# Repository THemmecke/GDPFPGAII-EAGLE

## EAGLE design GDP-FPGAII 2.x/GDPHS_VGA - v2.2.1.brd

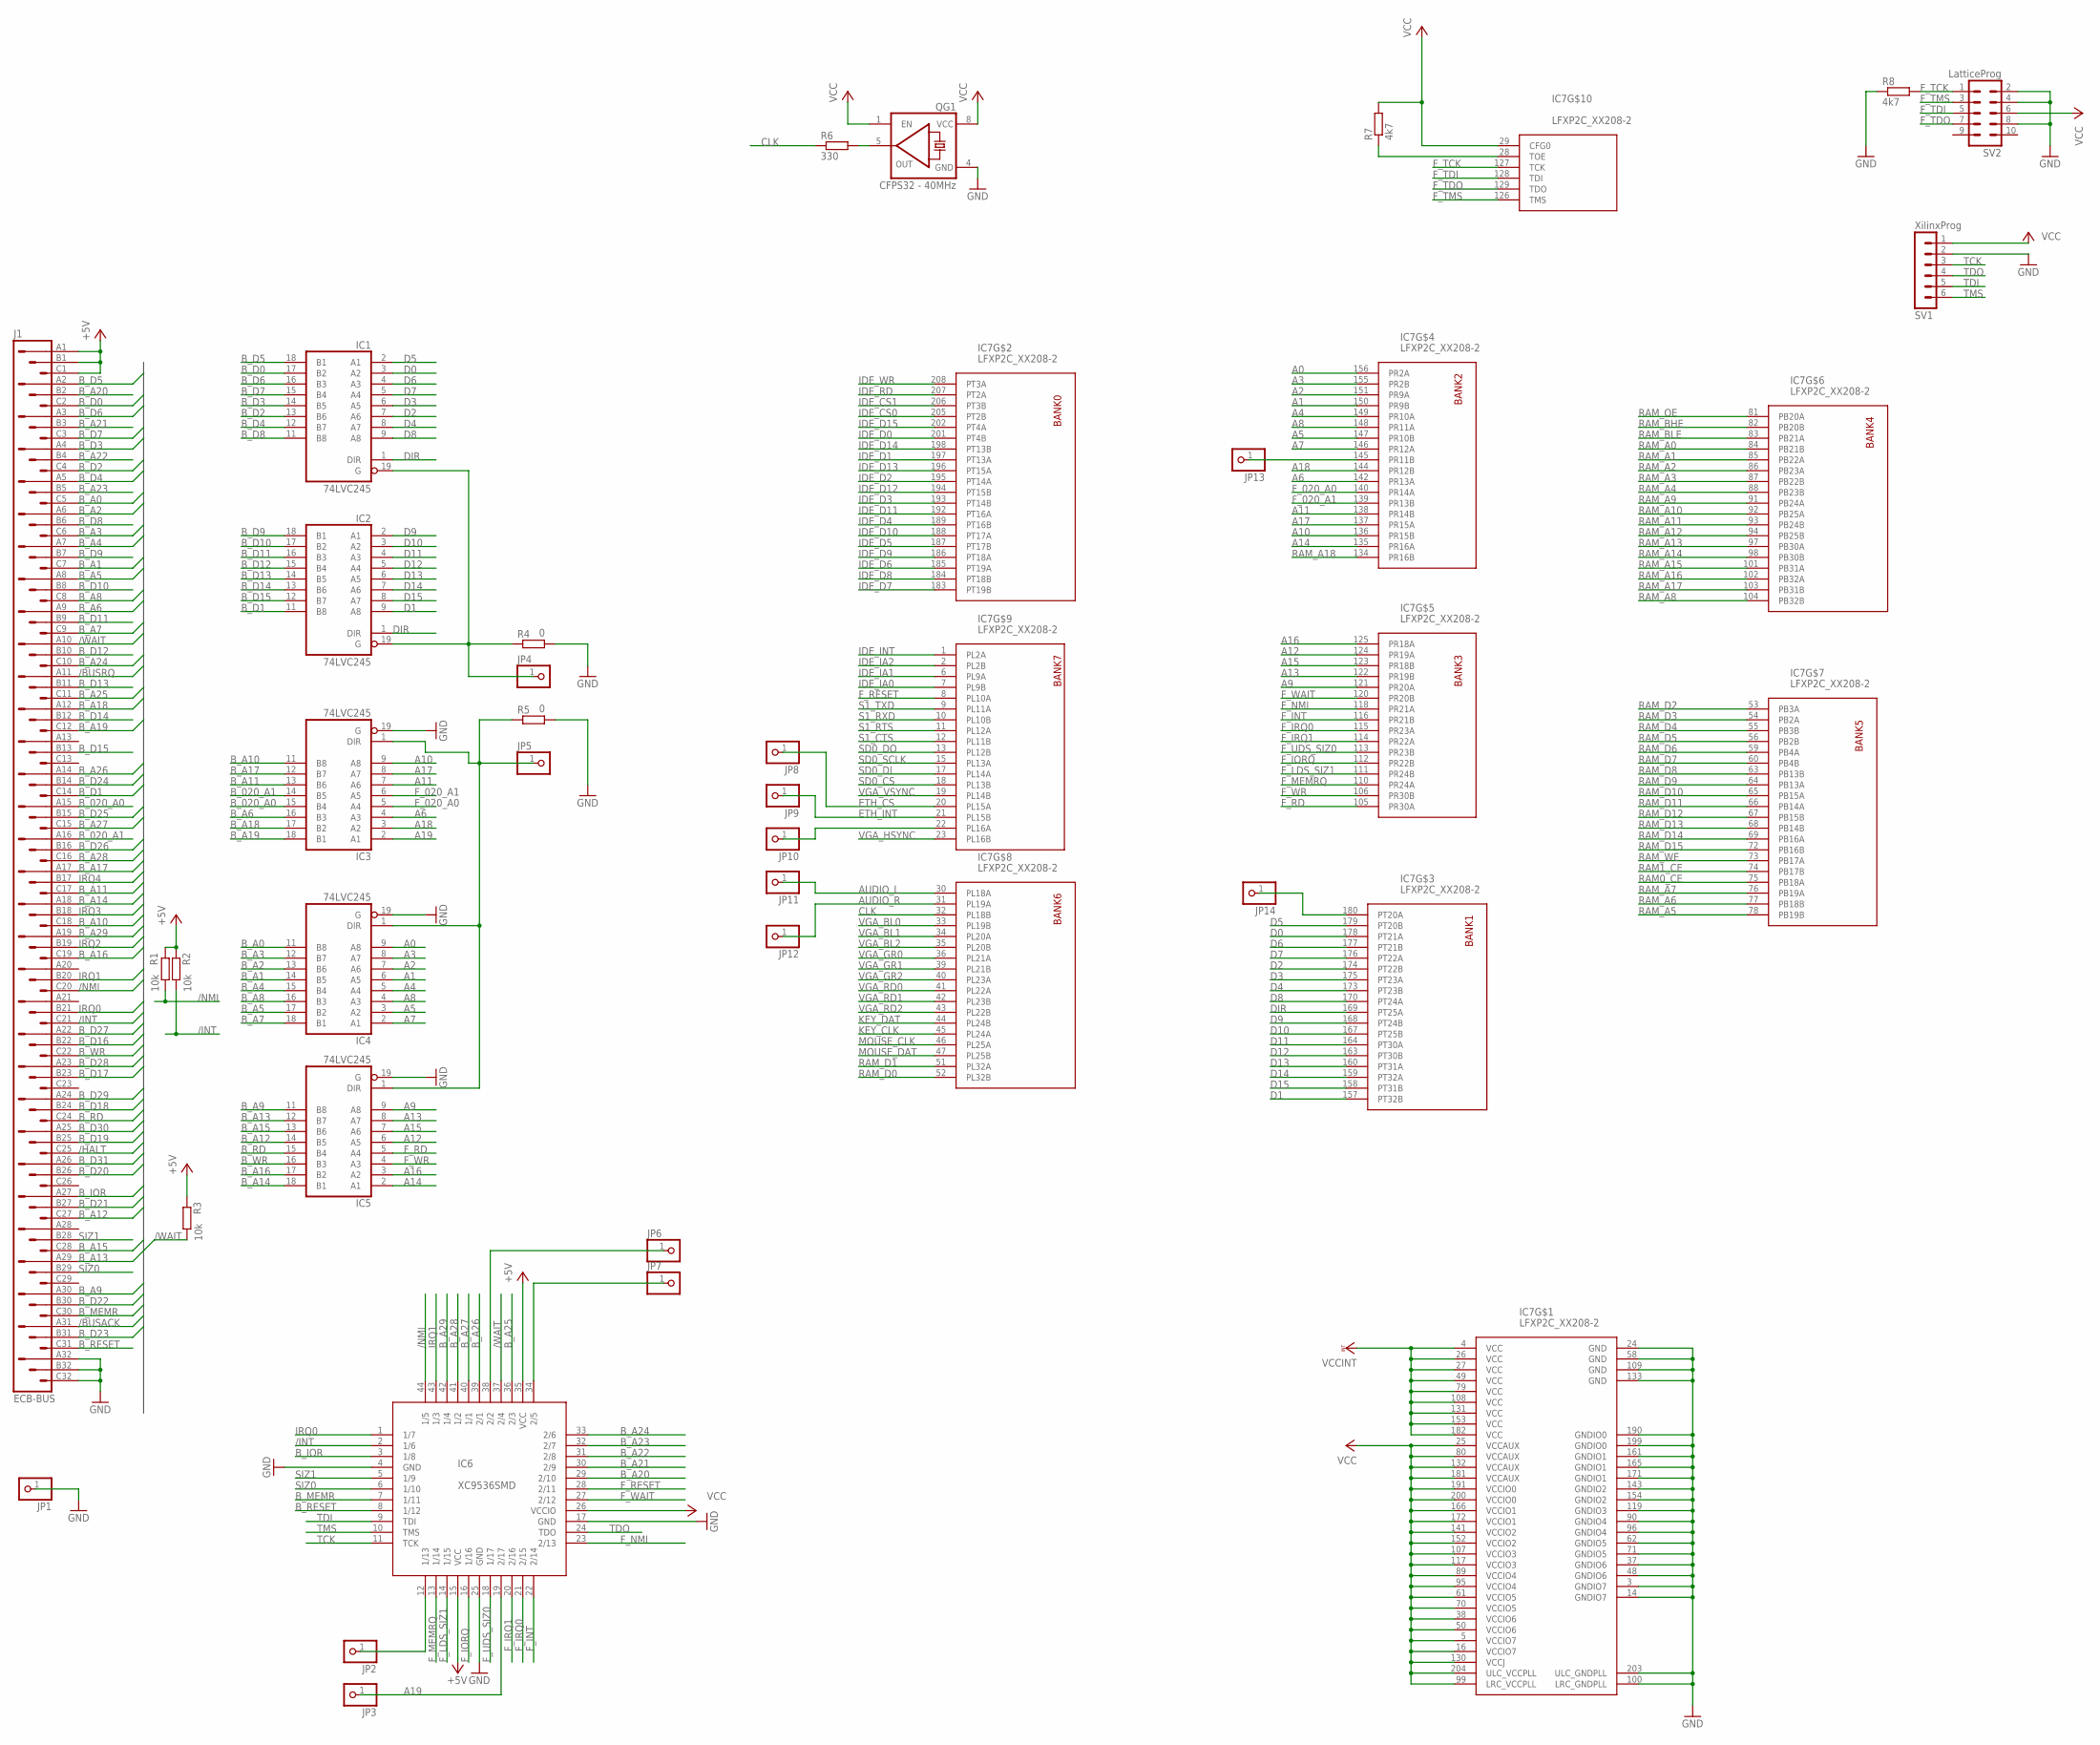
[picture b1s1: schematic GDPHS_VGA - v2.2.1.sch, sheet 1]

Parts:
IC1, IC2, IC3, IC4, IC5: 74LVC245; SO20W
IC6: XC9536SMD; TQFP44
IC7: LFXP2C_XX208-2; PQFP_208; MPN LFXP2-8E-5QN208C
J1: ECB-BUS; VG96K
JP1, JP2, JP3, JP4, JP5, JP6, JP7, JP8, JP9, JP10, JP11, JP12, JP13, JP14: PINHD-1X1; 1X01
QG1: CFPS32 - 40MHz; CFPS7X
R1, R2, R3: 10k; M0805
R4, R5: 0; M0805
R6: 330; M0805
R7, R8: 4k7; M0805
SV1: XilinxProg; MA06-1
SV2: LatticeProg; MA05-2

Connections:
$34: IC6.38 (2/2), JP6.1
+5V: IC6.15 (VCC), IC6.35 (VCC), J1.A1, J1.B1, J1.C1, R1.2, R2.2, R3.2; also elsewhere on the board
/BUSACK: J1.A31
/BUSRQ: J1.A11
/HALT: J1.C25
/INT: IC6.2 (1/6), J1.C21, R2.1
/NMI: IC6.44 (1/5), J1.C20, R1.1
/WAIT: IC6.37 (2/4), J1.A10, R3.1
A0: IC4.9 (A8), IC7.156 (PR2A)
A1: IC4.6 (A5), IC7.150 (PR9B)
A2: IC4.7 (A6), IC7.151 (PR9A)
A3: IC4.8 (A7), IC7.155 (PR2B)
A4: IC4.5 (A4), IC7.149 (PR10A)
A5: IC4.3 (A2), IC7.147 (PR10B)
A6: IC3.4 (A3), IC7.142 (PR13A)
A7: IC4.2 (A1), IC7.146 (PR12A)
A8: IC4.4 (A3), IC7.148 (PR11A)
A9: IC5.9 (A8), IC7.121 (PR20A)
A10: IC3.9 (A8), IC7.136 (PR15B)
A11: IC3.7 (A6), IC7.138 (PR14B)
A12: IC5.6 (A5), IC7.124 (PR19A)
A13: IC5.8 (A7), IC7.122 (PR19B)
A14: IC5.2 (A1), IC7.135 (PR16A)
A15: IC5.7 (A6), IC7.123 (PR18B)
A16: IC5.3 (A2), IC7.125 (PR18A)
A17: IC3.8 (A7), IC7.137 (PR15A)
A18: IC3.3 (A2), IC7.144 (PR12B)
A19: IC3.2 (A1), IC6.19 (2/17), JP3.1
AUDIO_L: IC7.30 (PL18A), JP11.1; also elsewhere on the board
AUDIO_R: IC7.31 (PL19A), JP12.1; also elsewhere on the board
B_020_A0: IC3.15 (B4), J1.A15
B_020_A1: IC3.14 (B5), J1.A16
B_A0: IC4.11 (B8), J1.C5
B_A1: IC4.14 (B5), J1.C7
B_A2: IC4.13 (B6), J1.A6
B_A3: IC4.12 (B7), J1.C6
B_A4: IC4.15 (B4), J1.A7
B_A5: IC4.17 (B2), J1.A8
B_A6: IC3.16 (B3), J1.A9
B_A7: IC4.18 (B1), J1.C9
B_A8: IC4.16 (B3), J1.C8
B_A9: IC5.11 (B8), J1.A30
B_A10: IC3.11 (B8), J1.C18
B_A11: IC3.13 (B6), J1.C17
B_A12: IC5.14 (B5), J1.C27
B_A13: IC5.12 (B7), J1.A29
B_A14: IC5.18 (B1), J1.A18
B_A15: IC5.13 (B6), J1.C28
B_A16: IC5.17 (B2), J1.C19
B_A17: IC3.12 (B7), J1.A17
B_A18: IC3.17 (B2), J1.A12
B_A19: IC3.18 (B1), J1.C12
B_A20: IC6.29 (2/10), J1.B2
B_A21: IC6.30 (2/9), J1.B3
B_A22: IC6.31 (2/8), J1.B4
B_A23: IC6.32 (2/7), J1.B5
B_A24: IC6.33 (2/6), J1.C10
B_A25: IC6.36 (2/3), J1.C11
B_A26: IC6.39 (2/1), J1.A14
B_A27: IC6.40 (1/1), J1.C15
B_A28: IC6.41 (1/2), J1.C16
B_A29: IC6.42 (1/4), J1.A19
B_D0: IC1.17 (B2), J1.C2
B_D1: IC2.11 (B8), J1.C14
B_D2: IC1.13 (B6), J1.C4
B_D3: IC1.14 (B5), J1.A4
B_D4: IC1.12 (B7), J1.A5
B_D5: IC1.18 (B1), J1.A2
B_D6: IC1.16 (B3), J1.A3
B_D7: IC1.15 (B4), J1.C3
B_D8: IC1.11 (B8), J1.B6
B_D9: IC2.18 (B1), J1.B7
B_D10: IC2.17 (B2), J1.B8
B_D11: IC2.16 (B3), J1.B9
B_D12: IC2.15 (B4), J1.B10
B_D13: IC2.14 (B5), J1.B11
B_D14: IC2.13 (B6), J1.B12
B_D15: IC2.12 (B7), J1.B13
B_D16: J1.B22
B_D17: J1.B23
B_D18: J1.B24
B_D19: J1.B25
B_D20: J1.B26
B_D21: J1.B27
B_D22: J1.B30
B_D23: J1.B31
B_D24: J1.B14
B_D25: J1.B15
B_D26: J1.B16
B_D27: J1.A22
B_D28: J1.A23
B_D29: J1.A24
B_D30: J1.A25
B_D31: J1.A26
B_IOR: IC6.3 (1/8), J1.A27
B_MEMR: IC6.7 (1/11), J1.C30
B_RD: IC5.15 (B4), J1.C24
B_RESET: IC6.8 (1/12), J1.C31
B_WR: IC5.16 (B3), J1.C22
CLK: IC7.32 (PL18B), R6.1
D0: IC1.3 (A2), IC7.178 (PT21A)
D1: IC2.9 (A8), IC7.157 (PT32B)
D2: IC1.7 (A6), IC7.174 (PT22B)
D3: IC1.6 (A5), IC7.175 (PT23A)
D4: IC1.8 (A7), IC7.173 (PT23B)
D5: IC1.2 (A1), IC7.179 (PT20B)
D6: IC1.4 (A3), IC7.177 (PT21B)
D7: IC1.5 (A4), IC7.176 (PT22A)
D8: IC1.9 (A8), IC7.170 (PT24A)
D9: IC2.2 (A1), IC7.168 (PT24B)
D10: IC2.3 (A2), IC7.167 (PT25B)
D11: IC2.4 (A3), IC7.164 (PT30A)
D12: IC2.5 (A4), IC7.163 (PT30B)
D13: IC2.6 (A5), IC7.160 (PT31A)
D14: IC2.7 (A6), IC7.159 (PT32A)
D15: IC2.8 (A7), IC7.158 (PT31B)
DIR: IC1.1 (DIR), IC2.1 (DIR), IC7.169 (PT25A)
ETH_CS: IC7.20 (PL15A), JP8.1; also elsewhere on the board
ETH_INT: IC7.21 (PL15B), JP9.1; also elsewhere on the board
F_020_A0: IC3.5 (A4), IC7.140 (PR14A)
F_020_A1: IC3.6 (A5), IC7.139 (PR13B)
F_INT: IC6.22 (2/14), IC7.116 (PR21B)
F_IORQ: IC6.16 (1/16), IC7.112 (PR22B)
F_IRQ0: IC6.21 (2/15), IC7.115 (PR23A)
F_IRQ1: IC6.20 (2/16), IC7.114 (PR22A)
F_LDS_SIZ1: IC6.14 (1/15), IC7.111 (PR24B)
F_MEMRQ: IC6.13 (1/14), IC7.110 (PR24A)
F_NMI: IC6.23 (2/13), IC7.118 (PR21A)
F_RD: IC5.5 (A4), IC7.105 (PR30A)
F_RESET: IC6.28 (2/11), IC7.8 (PL10A); also elsewhere on the board
F_TCK: IC7.127 (TCK), R8.2, SV2.1
F_TDI: IC7.128 (TDI), SV2.5
F_TDO: IC7.129 (TDO), SV2.7
F_TMS: IC7.126 (TMS), SV2.3
F_UDS_SIZ0: IC6.18 (1/17), IC7.113 (PR23B)
F_WAIT: IC6.27 (2/12), IC7.120 (PR20B)
F_WR: IC5.4 (A3), IC7.106 (PR30B)
GND: IC1.10 (GND), IC2.10 (GND), IC3.10 (GND), IC3.19 (G), IC4.10 (GND), IC4.19 (G), IC5.10 (GND), IC5.19 (G), IC6.4 (GND), IC6.17 (GND), IC6.25 (GND), IC7.3 (GNDIO7), IC7.14 (GNDIO7), IC7.24 (GND), IC7.37 (GNDIO6), IC7.48 (GNDIO6), IC7.58 (GND), IC7.62 (GNDIO5), IC7.71 (GNDIO5), IC7.90 (GNDIO4), IC7.96 (GNDIO4), IC7.100 (LRC_GNDPLL), IC7.109 (GND), IC7.119 (GNDIO3), IC7.133 (GND), IC7.143 (GNDIO2), IC7.154 (GNDIO2), IC7.161 (GNDIO1), IC7.165 (GNDIO1), IC7.171 (GNDIO1), IC7.190 (GNDIO0), IC7.199 (GNDIO0), IC7.203 (ULC_GNDPLL), J1.A32, J1.B32, J1.C32, JP1.1, QG1.4 (GND), R4.1, R5.1, R8.1, SV1.2, SV2.2, SV2.4, SV2.8; also elsewhere on the board
IDE_CS0: IC7.205 (PT2B); also elsewhere on the board
IDE_CS1: IC7.206 (PT3B); also elsewhere on the board
IDE_D0: IC7.201 (PT4B); also elsewhere on the board
IDE_D1: IC7.197 (PT13A); also elsewhere on the board
IDE_D2: IC7.195 (PT14A); also elsewhere on the board
IDE_D3: IC7.193 (PT14B); also elsewhere on the board
IDE_D4: IC7.189 (PT16B); also elsewhere on the board
IDE_D5: IC7.187 (PT17B); also elsewhere on the board
IDE_D6: IC7.185 (PT19A); also elsewhere on the board
IDE_D7: IC7.183 (PT19B); also elsewhere on the board
IDE_D8: IC7.184 (PT18B); also elsewhere on the board
IDE_D9: IC7.186 (PT18A); also elsewhere on the board
IDE_D10: IC7.188 (PT17A); also elsewhere on the board
IDE_D11: IC7.192 (PT16A); also elsewhere on the board
IDE_D12: IC7.194 (PT15B); also elsewhere on the board
IDE_D13: IC7.196 (PT15A); also elsewhere on the board
IDE_D14: IC7.198 (PT13B); also elsewhere on the board
IDE_D15: IC7.202 (PT4A); also elsewhere on the board
IDE_IA0: IC7.7 (PL9B); also elsewhere on the board
IDE_IA1: IC7.6 (PL9A); also elsewhere on the board
IDE_IA2: IC7.2 (PL2B); also elsewhere on the board
IDE_INT: IC7.1 (PL2A); also elsewhere on the board
IDE_RD: IC7.207 (PT2A); also elsewhere on the board
IDE_WR: IC7.208 (PT3A); also elsewhere on the board
IRQ0: IC6.1 (1/7), J1.B21
IRQ1: IC6.43 (1/3), J1.B20
IRQ2: J1.B19
IRQ3: J1.B18
IRQ4: J1.B17
KEY_CLK: IC7.45 (PL24A); also elsewhere on the board
KEY_DAT: IC7.44 (PL24B); also elsewhere on the board
MOUSE_CLK: IC7.46 (PL25A); also elsewhere on the board
MOUSE_DAT: IC7.47 (PL25B); also elsewhere on the board
unnamed: QG1.5 (OUT), R6.2
unnamed: IC7.22 (PL16A), JP10.1
unnamed: IC7.28 (TOE), R7.1
unnamed: IC7.145 (PR11B), JP13.1
unnamed: IC6.34 (2/5), JP7.1
unnamed: IC6.12 (1/13), JP2.1
unnamed: IC3.1 (DIR), IC4.1 (DIR), IC5.1 (DIR), JP5.1, R5.2
unnamed: IC1.19 (G), IC2.19 (G), JP4.1, R4.2
unnamed: IC7.180 (PT20A), JP14.1
RAM0_CE: IC7.75 (PB18A); also elsewhere on the board
RAM1_CE: IC7.74 (PB17B); also elsewhere on the board
RAM_A0: IC7.84 (PB21B); also elsewhere on the board
RAM_A1: IC7.85 (PB22A); also elsewhere on the board
RAM_A2: IC7.86 (PB23A); also elsewhere on the board
RAM_A3: IC7.87 (PB22B); also elsewhere on the board
RAM_A4: IC7.88 (PB23B); also elsewhere on the board
RAM_A5: IC7.78 (PB19B); also elsewhere on the board
RAM_A6: IC7.77 (PB18B); also elsewhere on the board
RAM_A7: IC7.76 (PB19A); also elsewhere on the board
RAM_A8: IC7.104 (PB32B); also elsewhere on the board
RAM_A9: IC7.91 (PB24A); also elsewhere on the board
RAM_A10: IC7.92 (PB25A); also elsewhere on the board
RAM_A11: IC7.93 (PB24B); also elsewhere on the board
RAM_A12: IC7.94 (PB25B); also elsewhere on the board
RAM_A13: IC7.97 (PB30A); also elsewhere on the board
RAM_A14: IC7.98 (PB30B); also elsewhere on the board
RAM_A15: IC7.101 (PB31A); also elsewhere on the board
RAM_A16: IC7.102 (PB32A); also elsewhere on the board
RAM_A17: IC7.103 (PB31B); also elsewhere on the board
RAM_A18: IC7.134 (PR16B); also elsewhere on the board
RAM_BHE: IC7.82 (PB20B); also elsewhere on the board
RAM_BLE: IC7.83 (PB21A); also elsewhere on the board
RAM_D0: IC7.52 (PL32B); also elsewhere on the board
RAM_D1: IC7.51 (PL32A); also elsewhere on the board
RAM_D2: IC7.53 (PB3A); also elsewhere on the board
RAM_D3: IC7.54 (PB2A); also elsewhere on the board
RAM_D4: IC7.55 (PB3B); also elsewhere on the board
RAM_D5: IC7.56 (PB2B); also elsewhere on the board
RAM_D6: IC7.59 (PB4A); also elsewhere on the board
RAM_D7: IC7.60 (PB4B); also elsewhere on the board
RAM_D8: IC7.63 (PB13B); also elsewhere on the board
RAM_D9: IC7.64 (PB13A); also elsewhere on the board
RAM_D10: IC7.65 (PB15A); also elsewhere on the board
RAM_D11: IC7.66 (PB14A); also elsewhere on the board
RAM_D12: IC7.67 (PB15B); also elsewhere on the board
RAM_D13: IC7.68 (PB14B); also elsewhere on the board
RAM_D14: IC7.69 (PB16A); also elsewhere on the board
RAM_D15: IC7.72 (PB16B); also elsewhere on the board
RAM_OE: IC7.81 (PB20A); also elsewhere on the board
RAM_WE: IC7.73 (PB17A); also elsewhere on the board
S1_CTS: IC7.12 (PL11B); also elsewhere on the board
S1_RTS: IC7.11 (PL12A); also elsewhere on the board
S1_RXD: IC7.10 (PL10B); also elsewhere on the board
S1_TXD: IC7.9 (PL11A); also elsewhere on the board
SD0_CS: IC7.18 (PL13B); also elsewhere on the board
SD0_DI: IC7.17 (PL14A); also elsewhere on the board
SD0_DO: IC7.13 (PL12B); also elsewhere on the board
SD0_SCLK: IC7.15 (PL13A); also elsewhere on the board
SIZ0: IC6.6 (1/10), J1.B29
SIZ1: IC6.5 (1/9), J1.B28
TCK: IC6.11 (TCK), SV1.3
TDI: IC6.9 (TDI), SV1.5
TDO: IC6.24 (TDO), SV1.4
TMS: IC6.10 (TMS), SV1.6
VCC: IC1.20 (VCC), IC2.20 (VCC), IC3.20 (VCC), IC4.20 (VCC), IC5.20 (VCC), IC6.26 (VCCIO), IC7.5 (VCCIO7), IC7.16 (VCCIO7), IC7.25 (VCCAUX), IC7.29 (CFG0), IC7.38 (VCCIO6), IC7.50 (VCCIO6), IC7.61 (VCCIO5), IC7.70 (VCCIO5), IC7.80 (VCCAUX), IC7.89 (VCCIO4), IC7.95 (VCCIO4), IC7.99 (LRC_VCCPLL), IC7.107 (VCCIO3), IC7.117 (VCCIO3), IC7.130 (VCCJ), IC7.132 (VCCAUX), IC7.141 (VCCIO2), IC7.152 (VCCIO2), IC7.166 (VCCIO1), IC7.172 (VCCIO1), IC7.181 (VCCAUX), IC7.191 (VCCIO0), IC7.200 (VCCIO0), IC7.204 (ULC_VCCPLL), QG1.1 (EN), QG1.8 (VCC), R7.2, SV1.1, SV2.6; also elsewhere on the board
VCCINT: IC7.4 (VCC), IC7.26 (VCC), IC7.27 (VCC), IC7.49 (VCC), IC7.79 (VCC), IC7.108 (VCC), IC7.131 (VCC), IC7.153 (VCC), IC7.182 (VCC); also elsewhere on the board
VGA_BL0: IC7.33 (PL19B); also elsewhere on the board
VGA_BL1: IC7.34 (PL20A); also elsewhere on the board
VGA_BL2: IC7.35 (PL20B); also elsewhere on the board
VGA_GR0: IC7.36 (PL21A); also elsewhere on the board
VGA_GR1: IC7.39 (PL21B); also elsewhere on the board
VGA_GR2: IC7.40 (PL23A); also elsewhere on the board
VGA_HSYNC: IC7.23 (PL16B); also elsewhere on the board
VGA_RD0: IC7.41 (PL22A); also elsewhere on the board
VGA_RD1: IC7.42 (PL23B); also elsewhere on the board
VGA_RD2: IC7.43 (PL22B); also elsewhere on the board
VGA_VSYNC: IC7.19 (PL14B); also elsewhere on the board

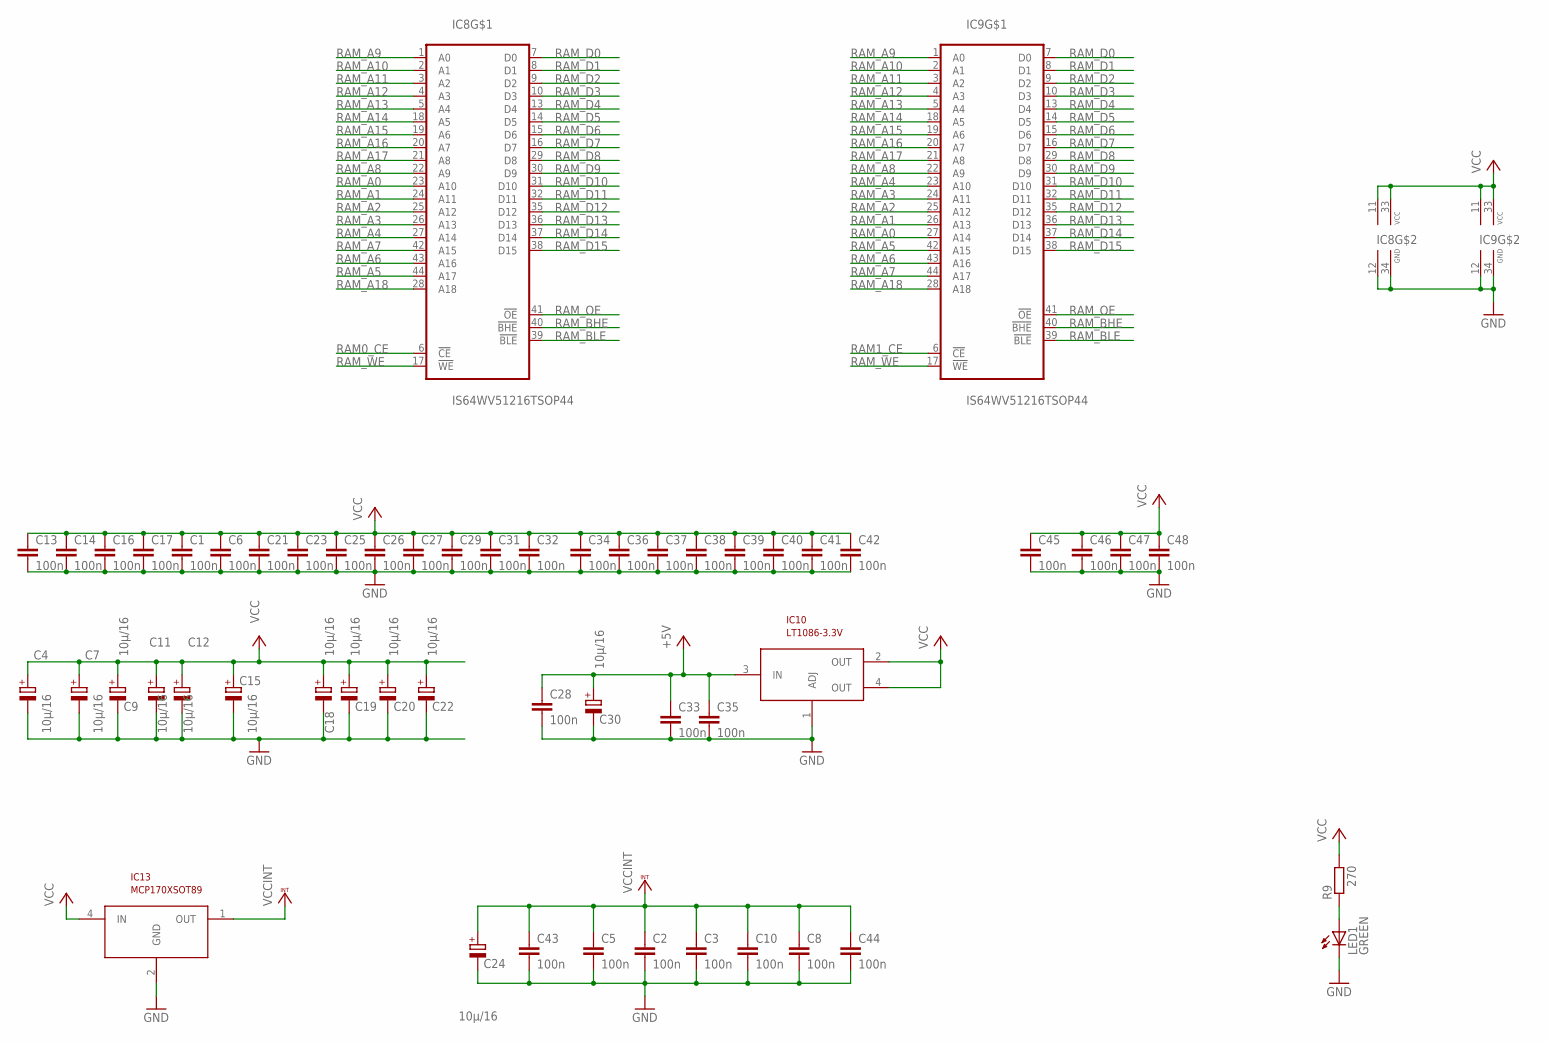
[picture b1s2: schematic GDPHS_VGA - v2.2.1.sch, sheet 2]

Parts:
C1, C2, C3, C5, C6, C8, C10, C13, C14, C16, C17, C21, C23, C25, C26, C27, C28, C29, C31, C32, C33, C34, C35, C36, C37, C38, C39, C40, C41, C42, C43, C44, C45, C46, C47, C48: 100n; C0805
C4, C7, C9, C11, C12, C15, C18, C19, C20, C22, C24, C30: 10µ/16; SMC_C
IC8, IC9: IS64WV51216TSOP44; TSOP44-400; MPN CY7C1051DV33-10ZSXI
IC10: LT1086-3.3V; MDD
IC13: MCP170XSOT89; SOT89-W
LED1: GREEN; CHIPLED_0805
R9: 270; M0805

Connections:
+5V: C28.1, C30.+, C33.1, C35.1, IC10.3 (IN); also elsewhere on the board
GND: C1.2, C2.2, C3.2, C4.-, C5.2, C6.2, C7.-, C8.2, C9.-, C10.2, C11.-, C12.-, C13.2, C14.2, C15.-, C16.2, C17.2, C18.-, C19.-, C20.-, C21.2, C22.-, C23.2, C24.-, C25.2, C26.2, C27.2, C28.2, C29.2, C30.-, C31.2, C32.2, C33.2, C34.2, C35.2, C36.2, C37.2, C38.2, C39.2, C40.2, C41.2, C42.2, C43.2, C44.2, C45.2, C46.2, C47.2, C48.2, IC8.12 (GND), IC8.34 (GND), IC9.12 (GND), IC9.34 (GND), IC10.1 (ADJ), IC13.2 (GND), LED1.C; also elsewhere on the board
unnamed: LED1.A, R9.1
RAM0_CE: IC8.6 (!CE); also elsewhere on the board
RAM1_CE: IC9.6 (!CE); also elsewhere on the board
RAM_A0: IC8.23 (A10), IC9.27 (A14); also elsewhere on the board
RAM_A1: IC8.24 (A11), IC9.26 (A13); also elsewhere on the board
RAM_A2: IC8.25 (A12), IC9.25 (A12); also elsewhere on the board
RAM_A3: IC8.26 (A13), IC9.24 (A11); also elsewhere on the board
RAM_A4: IC8.27 (A14), IC9.23 (A10); also elsewhere on the board
RAM_A5: IC8.44 (A17), IC9.42 (A15); also elsewhere on the board
RAM_A6: IC8.43 (A16), IC9.43 (A16); also elsewhere on the board
RAM_A7: IC8.42 (A15), IC9.44 (A17); also elsewhere on the board
RAM_A8: IC8.22 (A9), IC9.22 (A9); also elsewhere on the board
RAM_A9: IC8.1 (A0), IC9.1 (A0); also elsewhere on the board
RAM_A10: IC8.2 (A1), IC9.2 (A1); also elsewhere on the board
RAM_A11: IC8.3 (A2), IC9.3 (A2); also elsewhere on the board
RAM_A12: IC8.4 (A3), IC9.4 (A3); also elsewhere on the board
RAM_A13: IC8.5 (A4), IC9.5 (A4); also elsewhere on the board
RAM_A14: IC8.18 (A5), IC9.18 (A5); also elsewhere on the board
RAM_A15: IC8.19 (A6), IC9.19 (A6); also elsewhere on the board
RAM_A16: IC8.20 (A7), IC9.20 (A7); also elsewhere on the board
RAM_A17: IC8.21 (A8), IC9.21 (A8); also elsewhere on the board
RAM_A18: IC8.28 (A18), IC9.28 (A18); also elsewhere on the board
RAM_BHE: IC8.40 (!BHE), IC9.40 (!BHE); also elsewhere on the board
RAM_BLE: IC8.39 (!BLE), IC9.39 (!BLE); also elsewhere on the board
RAM_D0: IC8.7 (D0), IC9.7 (D0); also elsewhere on the board
RAM_D1: IC8.8 (D1), IC9.8 (D1); also elsewhere on the board
RAM_D2: IC8.9 (D2), IC9.9 (D2); also elsewhere on the board
RAM_D3: IC8.10 (D3), IC9.10 (D3); also elsewhere on the board
RAM_D4: IC8.13 (D4), IC9.13 (D4); also elsewhere on the board
RAM_D5: IC8.14 (D5), IC9.14 (D5); also elsewhere on the board
RAM_D6: IC8.15 (D6), IC9.15 (D6); also elsewhere on the board
RAM_D7: IC8.16 (D7), IC9.16 (D7); also elsewhere on the board
RAM_D8: IC8.29 (D8), IC9.29 (D8); also elsewhere on the board
RAM_D9: IC8.30 (D9), IC9.30 (D9); also elsewhere on the board
RAM_D10: IC8.31 (D10), IC9.31 (D10); also elsewhere on the board
RAM_D11: IC8.32 (D11), IC9.32 (D11); also elsewhere on the board
RAM_D12: IC8.35 (D12), IC9.35 (D12); also elsewhere on the board
RAM_D13: IC8.36 (D13), IC9.36 (D13); also elsewhere on the board
RAM_D14: IC8.37 (D14), IC9.37 (D14); also elsewhere on the board
RAM_D15: IC8.38 (D15), IC9.38 (D15); also elsewhere on the board
RAM_OE: IC8.41 (!OE), IC9.41 (!OE); also elsewhere on the board
RAM_WE: IC8.17 (!WE), IC9.17 (!WE); also elsewhere on the board
VCC: C1.1, C4.+, C6.1, C7.+, C9.+, C11.+, C12.+, C13.1, C14.1, C15.+, C16.1, C17.1, C18.+, C19.+, C20.+, C21.1, C22.+, C23.1, C25.1, C26.1, C27.1, C29.1, C31.1, C32.1, C34.1, C36.1, C37.1, C38.1, C39.1, C40.1, C41.1, C42.1, C45.1, C46.1, C47.1, C48.1, IC8.11 (VCC), IC8.33 (VCC2), IC9.11 (VCC), IC9.33 (VCC2), IC10.2 (OUT), IC10.4 (OUT), IC13.4 (IN), R9.2; also elsewhere on the board
VCCINT: C2.1, C3.1, C5.1, C8.1, C10.1, C24.+, C43.1, C44.1, IC13.1 (OUT); also elsewhere on the board

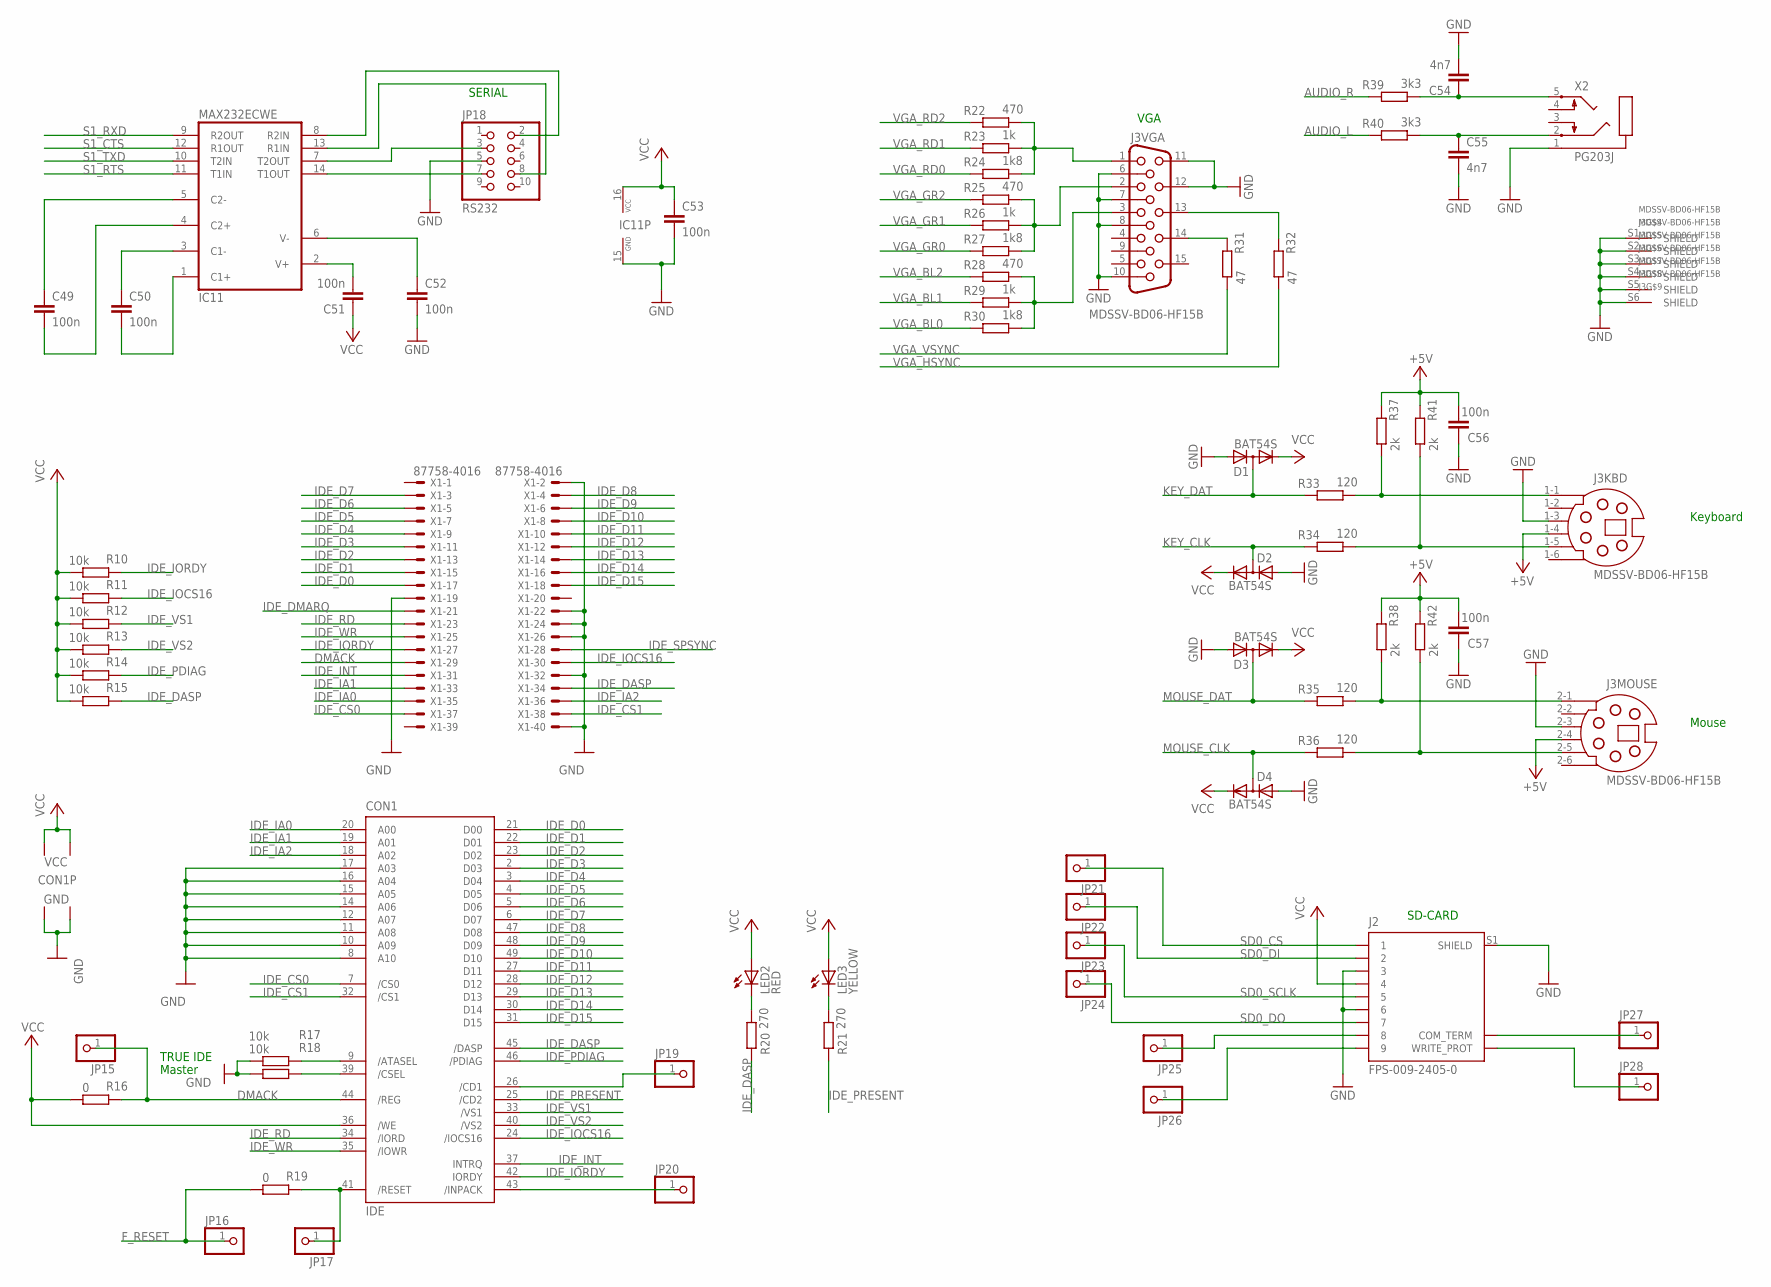
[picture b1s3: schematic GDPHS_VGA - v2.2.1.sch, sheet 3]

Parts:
C49, C50, C51, C52, C53, C56, C57: 100n; C0805
C54, C55: 4n7; C0805
CON1: IDE; CF-050-P2-X03-10-DS-1
D1, D2, D3, D4: BAT54S; SOT23
IC11: MAX232ECWE; SO16L
J2: FPS-009-2405-0
J3: MDSSV-BD06-HF15B; MDSSV-BD06-HF15-B
JP15, JP16, JP17, JP19, JP20, JP21, JP22, JP23, JP24, JP25, JP26, JP27, JP28: PINHD-1X1; 1X01
JP18: RS232; 2X05
LED2: RED; CHIPLED_0805
LED3: YELLOW; CHIPLED_0805
R10, R11, R12, R13, R14, R15, R17, R18: 10k; M0805
R16, R19: 0; M0805
R20, R21: 270; M0805
R22, R25, R28: 470; M0805
R23, R26, R29: 1k; M0805
R24, R27, R30: 1k8; M0805
R31, R32: 47; M0805
R33, R34, R35, R36: 120; M0805
R37, R38, R41, R42: 2k; M0805
R39, R40: 3k3; M0805
X1: 87758-4016
X2: PG203J

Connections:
+5V: C56.2, C57.2, J3.1-4 (4), J3.2-4 (4), R37.1, R38.1, R41.1, R42.1; also elsewhere on the board
AUDIO_L: R40.1; also elsewhere on the board
AUDIO_R: R39.1; also elsewhere on the board
DMACK: CON1.44 (/REG), JP15.1, R16.1, X1.29
F_RESET: JP16.1, R19.2; also elsewhere on the board
GND: C52.2, C53.2, C54.2, C55.2, C56.1, C57.1, CON1.1 (GND1), CON1.8 (A10), CON1.10 (A09), CON1.11 (A08), CON1.12 (A07), CON1.14 (A06), CON1.15 (A05), CON1.16 (A04), CON1.17 (A03), CON1.50 (GND2), D1.1 (A), D2.1 (A), D3.1 (A), D4.1 (A), IC11.15 (GND), J2.3, J2.6, J2.S1 (SHIELD), J3.1-3 (3), J3.2-3 (3), J3.6, J3.7, J3.8, J3.10, J3.11, J3.12, J3.S1 (SHIELD), J3.S2 (SHIELD), J3.S3 (SHIELD), J3.S4 (SHIELD), J3.S5 (SHIELD), J3.S6 (SHIELD), JP18.5, R17.2, R18.2, X1.2, X1.19, X1.22, X1.24, X1.26, X1.32, X1.40, X2.1; also elsewhere on the board
IDE_CS0: CON1.7 (/CS0), X1.37; also elsewhere on the board
IDE_CS1: CON1.32 (/CS1), X1.38; also elsewhere on the board
IDE_D0: CON1.21 (D00), X1.17; also elsewhere on the board
IDE_D1: CON1.22 (D01), X1.15; also elsewhere on the board
IDE_D2: CON1.23 (D02), X1.13; also elsewhere on the board
IDE_D3: CON1.2 (D03), X1.11; also elsewhere on the board
IDE_D4: CON1.3 (D04), X1.9; also elsewhere on the board
IDE_D5: CON1.4 (D05), X1.7; also elsewhere on the board
IDE_D6: CON1.5 (D06), X1.5; also elsewhere on the board
IDE_D7: CON1.6 (D07), X1.3; also elsewhere on the board
IDE_D8: CON1.47 (D08), X1.4; also elsewhere on the board
IDE_D9: CON1.48 (D09), X1.6; also elsewhere on the board
IDE_D10: CON1.49 (D10), X1.8; also elsewhere on the board
IDE_D11: CON1.27 (D11), X1.10; also elsewhere on the board
IDE_D12: CON1.28 (D12), X1.12; also elsewhere on the board
IDE_D13: CON1.29 (D13), X1.14; also elsewhere on the board
IDE_D14: CON1.30 (D14), X1.16; also elsewhere on the board
IDE_D15: CON1.31 (D15), X1.18; also elsewhere on the board
IDE_DASP: CON1.45 (/DASP), R15.1, R20.1, X1.34
IDE_DMARQ: X1.21
IDE_IA0: CON1.20 (A00), X1.35; also elsewhere on the board
IDE_IA1: CON1.19 (A01), X1.33; also elsewhere on the board
IDE_IA2: CON1.18 (A02), X1.36; also elsewhere on the board
IDE_INT: CON1.37 (INTRQ), X1.31; also elsewhere on the board
IDE_IOCS16: CON1.24 (/IOCS16), R11.1, X1.30
IDE_IORDY: CON1.42 (IORDY), R10.1, X1.27
IDE_PDIAG: CON1.46 (/PDIAG), R14.1
IDE_PRESENT: CON1.25 (/CD2), R21.1
IDE_RD: CON1.34 (/IORD), X1.23; also elsewhere on the board
IDE_SPSYNC: X1.28
IDE_VS1: CON1.33 (/VS1), R12.1
IDE_VS2: CON1.40 (/VS2), R13.1
IDE_WR: CON1.35 (/IOWR), X1.25; also elsewhere on the board
KEY_CLK: D2.3 (AC), R34.1; also elsewhere on the board
KEY_DAT: D1.3 (AC), R33.1; also elsewhere on the board
MOUSE_CLK: D4.3 (AC), R36.1; also elsewhere on the board
MOUSE_DAT: D3.3 (AC), R35.1; also elsewhere on the board
unnamed: C50.2, IC11.1 (C1+)
unnamed: LED2.C, R20.2
unnamed: C50.1, IC11.3 (C1-)
unnamed: C49.2, IC11.4 (C2+)
unnamed: C49.1, IC11.5 (C2-)
unnamed: C52.1, IC11.6 (V-)
unnamed: C51.2, IC11.2 (V+)
unnamed: LED3.C, R21.2
unnamed: IC11.8 (R2IN), JP18.2
unnamed: IC11.13 (R1IN), JP18.8
unnamed: IC11.7 (T2OUT), JP18.3
unnamed: J3.1, R22.2, R23.2, R24.2
unnamed: J3.2, R25.2, R26.2, R27.2
unnamed: J3.3, R28.2, R29.2, R30.2
unnamed: J3.13, R32.1
unnamed: J3.14, R31.1
unnamed: J3.1-1 (1), R33.2, R37.2
unnamed: J3.1-5 (5), R34.2, R41.2
unnamed: J3.2-1 (1), R35.2, R38.2
unnamed: J3.2-5 (5), R36.2, R42.2
unnamed: CON1.39 (/CSEL), R18.1
unnamed: CON1.9 (/ATASEL), R17.1
unnamed: C54.1, R39.2, X2.5
unnamed: C55.1, R40.2, X2.2
unnamed: IC11.14 (T1OUT), JP18.7
unnamed: CON1.41 (/RESET), JP17.1, R19.1
unnamed: CON1.43 (/INPACK), JP20.1
unnamed: CON1.26 (/CD1), JP19.1
unnamed: J2.8, JP25.1
unnamed: J2.9, JP26.1
unnamed: J2.CD (COM_TERM), JP27.1
unnamed: J2.WP (WRITE_PROT), JP28.1
S1_CTS: IC11.12 (R1OUT); also elsewhere on the board
S1_RTS: IC11.11 (T1IN); also elsewhere on the board
S1_RXD: IC11.9 (R2OUT); also elsewhere on the board
S1_TXD: IC11.10 (T2IN); also elsewhere on the board
SD0_CS: J2.1, JP21.1; also elsewhere on the board
SD0_DI: J2.2, JP22.1; also elsewhere on the board
SD0_DO: J2.7, JP24.1; also elsewhere on the board
SD0_SCLK: J2.5, JP23.1; also elsewhere on the board
VCC: C51.1, C53.1, CON1.13 (VCC2), CON1.36 (/WE), CON1.38 (VCC1), D1.2 (C), D2.2 (C), D3.2 (C), D4.2 (C), IC11.16 (VCC), J2.4, LED2.A, LED3.A, R10.2, R11.2, R12.2, R13.2, R14.2, R15.2, R16.2; also elsewhere on the board
VGA_BL0: R30.1; also elsewhere on the board
VGA_BL1: R29.1; also elsewhere on the board
VGA_BL2: R28.1; also elsewhere on the board
VGA_GR0: R27.1; also elsewhere on the board
VGA_GR1: R26.1; also elsewhere on the board
VGA_GR2: R25.1; also elsewhere on the board
VGA_HSYNC: R32.2; also elsewhere on the board
VGA_RD0: R24.1; also elsewhere on the board
VGA_RD1: R23.1; also elsewhere on the board
VGA_RD2: R22.1; also elsewhere on the board
VGA_VSYNC: R31.2; also elsewhere on the board

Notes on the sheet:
SERIAL
SD-CARD
VGA
Keyboard
Mouse
Master
TRUE IDE

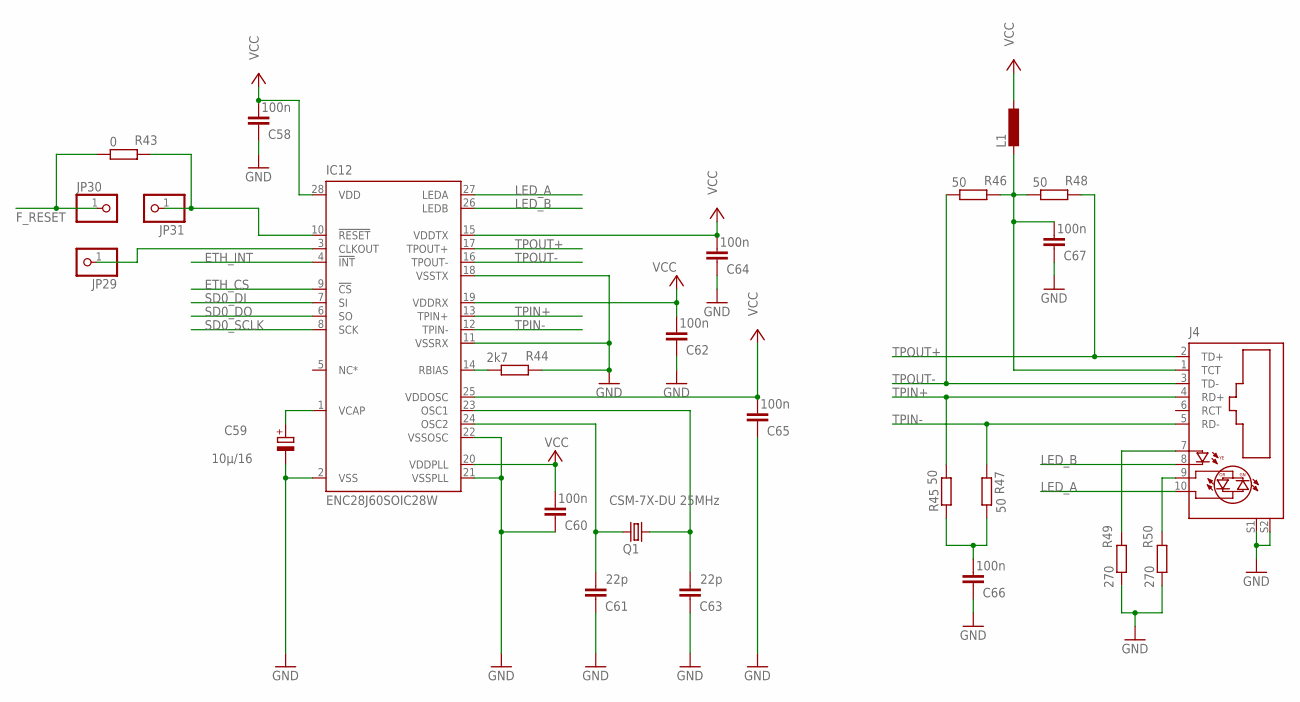
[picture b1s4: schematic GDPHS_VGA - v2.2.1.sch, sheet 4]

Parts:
C58, C60, C62, C64, C65, C66, C67: 100n; C0805
C59: 10µ/16; SMC_C
C61, C63: 22p; C0805
IC12: ENC28J60SOIC28W; SO28W
J4: 08B0-1X1T-36-F08B0-1X1T-36-F; 08B0-1X1T-36-F
JP29, JP30, JP31: PINHD-1X1; 1X01
L1: L-EUL1206; L1206
Q1: CSM-7X-DU 25MHz; CSM-7X-DU; MPN CS10-25.000MABJTR
R43: 0; M0805
R44: 2k7; M0805
R45, R46, R47, R48: 50; M0805
R49, R50: 270; M0805

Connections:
ETH_CS: IC12.9 (!CS); also elsewhere on the board
ETH_INT: IC12.4 (!INT); also elsewhere on the board
F_RESET: JP30.1, R43.2; also elsewhere on the board
GND: C58.1, C59.-, C60.1, C61.1, C62.1, C63.1, C64.1, C65.1, C66.1, C67.1, IC12.2 (VSS), IC12.11 (VSSRX), IC12.18 (VSSTX), IC12.21 (VSSPLL), IC12.22 (VSSOSC), J4.S1, J4.S2, R44.1, R49.2, R50.2; also elsewhere on the board
LED_A: IC12.27 (LEDA), J4.10 (C1)
LED_B: IC12.26 (LEDB), J4.8 (C)
unnamed: J4.9 (A1), R50.1
unnamed: J4.7 (A), R49.1
unnamed: IC12.10 (!RESET), JP31.1, R43.1
unnamed: IC12.3 (CLKOUT), JP29.1
unnamed: C63.2, IC12.23 (OSC1), Q1.2
unnamed: C61.2, IC12.24 (OSC2), Q1.1
unnamed: C59.+, IC12.1 (VCAP)
unnamed: IC12.14 (RBIAS), R44.2
unnamed: C66.2, R45.1, R47.2
unnamed: C67.2, J4.1 (TCT), L1.2, R46.1, R48.2
SD0_DI: IC12.7 (SI); also elsewhere on the board
SD0_DO: IC12.6 (SO); also elsewhere on the board
SD0_SCLK: IC12.8 (SCK); also elsewhere on the board
TPIN+: IC12.13 (TPIN+), J4.4 (RD+), R45.2
TPIN-: IC12.12 (TPIN-), J4.5 (RD-), R47.1
TPOUT+: IC12.17 (TPOUT+), J4.2 (TD+), R48.1
TPOUT-: IC12.16 (TPOUT-), J4.3 (TD-), R46.2
VCC: C58.2, C60.2, C62.2, C64.2, C65.2, IC12.15 (VDDTX), IC12.19 (VDDRX), IC12.20 (VDDPLL), IC12.25 (VDDOSC), IC12.28 (VDD), L1.1; also elsewhere on the board
